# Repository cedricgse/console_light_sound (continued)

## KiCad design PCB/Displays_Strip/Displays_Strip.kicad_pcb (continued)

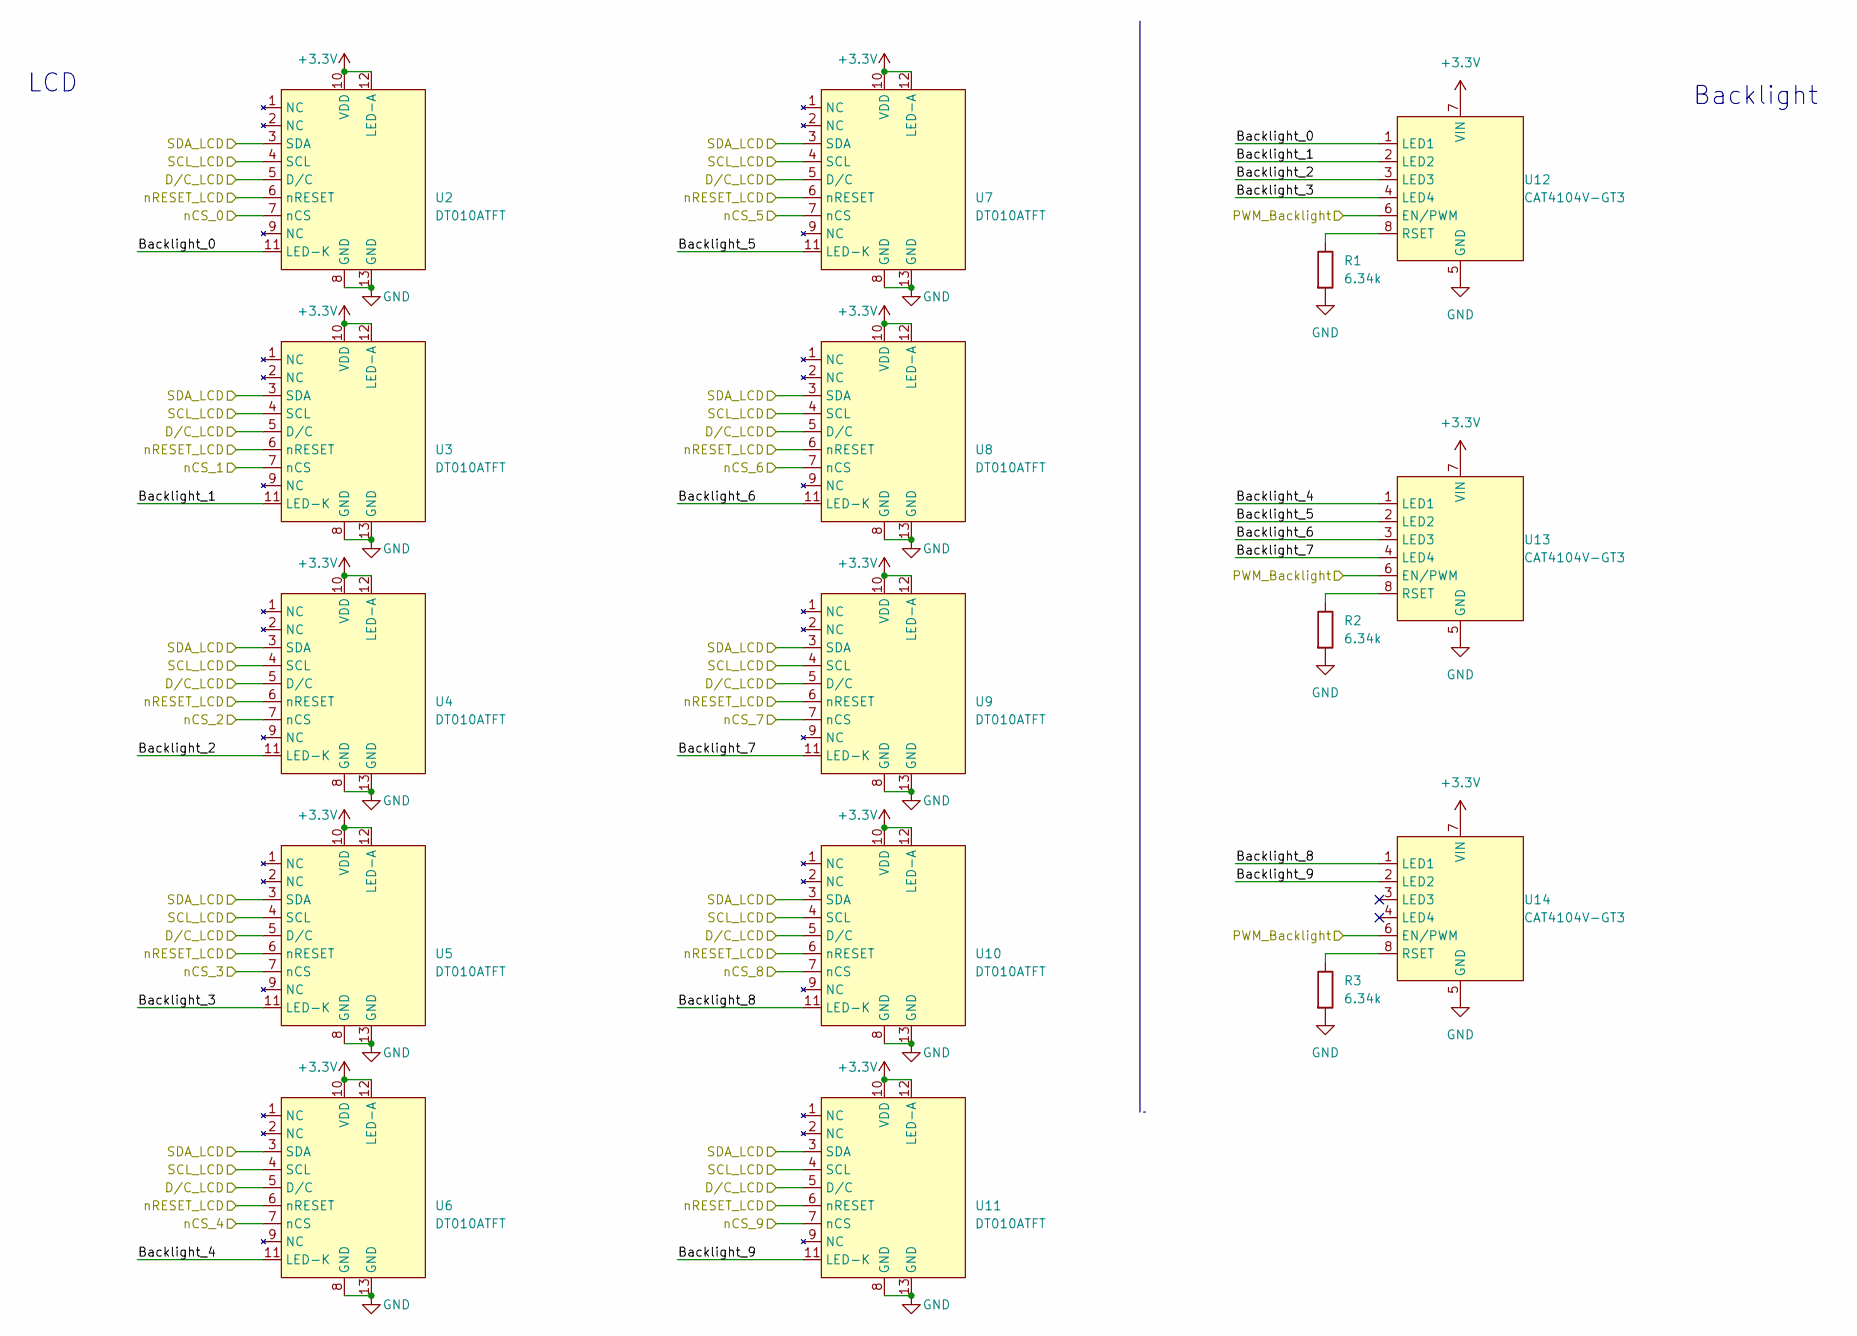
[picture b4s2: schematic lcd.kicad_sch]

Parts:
R1, R2, R3: 6.34k; R_0805_2012Metric
U2, U3, U4, U5, U6, U7, U8, U9, U10, U11: DT010ATFT; Hirose FFC FPC 13 Pin Inverted
U12, U13, U14: CAT4104V-GT3; SOIC-8_3.9x4.9mm_P1.27mm

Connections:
+3.3V: U2.10 (VDD), U2.12 (LED-A), U3.10 (VDD), U3.12 (LED-A), U4.10 (VDD), U4.12 (LED-A), U5.10 (VDD), U5.12 (LED-A), U6.10 (VDD), U6.12 (LED-A), U7.10 (VDD), U7.12 (LED-A), U8.10 (VDD), U8.12 (LED-A), U9.10 (VDD), U9.12 (LED-A), U10.10 (VDD), U10.12 (LED-A), U11.10 (VDD), U11.12 (LED-A), U12.7 (VIN), U13.7 (VIN), U14.7 (VIN); also elsewhere on the board
/D/C_LCD: U2.5 (D/C), U3.5 (D/C), U4.5 (D/C), U5.5 (D/C), U6.5 (D/C), U7.5 (D/C), U8.5 (D/C), U9.5 (D/C), U10.5 (D/C), U11.5 (D/C); also elsewhere on the board
/LCDs/Backlight_0: U2.11 (LED-K), U12.1 (LED1)
/LCDs/Backlight_1: U3.11 (LED-K), U12.2 (LED2)
/LCDs/Backlight_2: U4.11 (LED-K), U12.3 (LED3)
/LCDs/Backlight_3: U5.11 (LED-K), U12.4 (LED4)
/LCDs/Backlight_4: U6.11 (LED-K), U13.1 (LED1)
/LCDs/Backlight_5: U7.11 (LED-K), U13.2 (LED2)
/LCDs/Backlight_6: U8.11 (LED-K), U13.3 (LED3)
/LCDs/Backlight_7: U9.11 (LED-K), U13.4 (LED4)
/LCDs/Backlight_8: U10.11 (LED-K), U14.1 (LED1)
/LCDs/Backlight_9: U11.11 (LED-K), U14.2 (LED2)
/PWM_LCD: U12.6 (EN/PWM), U13.6 (EN/PWM), U14.6 (EN/PWM); also elsewhere on the board
/SCK_LCD: U2.4 (SCL), U3.4 (SCL), U4.4 (SCL), U5.4 (SCL), U6.4 (SCL), U7.4 (SCL), U8.4 (SCL), U9.4 (SCL), U10.4 (SCL), U11.4 (SCL); also elsewhere on the board
/SDA_LCD: U2.3 (SDA), U3.3 (SDA), U4.3 (SDA), U5.3 (SDA), U6.3 (SDA), U7.3 (SDA), U8.3 (SDA), U9.3 (SDA), U10.3 (SDA), U11.3 (SDA); also elsewhere on the board
/nCS_0: U2.7 (nCS); also elsewhere on the board
/nCS_1: U3.7 (nCS); also elsewhere on the board
/nCS_2: U4.7 (nCS); also elsewhere on the board
/nCS_3: U5.7 (nCS); also elsewhere on the board
/nCS_4: U6.7 (nCS); also elsewhere on the board
/nCS_5: U7.7 (nCS); also elsewhere on the board
/nCS_6: U8.7 (nCS); also elsewhere on the board
/nCS_7: U9.7 (nCS); also elsewhere on the board
/nCS_8: U10.7 (nCS); also elsewhere on the board
/nCS_9: U11.7 (nCS); also elsewhere on the board
/nRESET_LCD: U2.6 (nRESET), U3.6 (nRESET), U4.6 (nRESET), U5.6 (nRESET), U6.6 (nRESET), U7.6 (nRESET), U8.6 (nRESET), U9.6 (nRESET), U10.6 (nRESET), U11.6 (nRESET); also elsewhere on the board
GND: R1.2, R2.2, R3.2, U2.8 (GND), U2.13 (GND), U3.8 (GND), U3.13 (GND), U4.8 (GND), U4.13 (GND), U5.8 (GND), U5.13 (GND), U6.8 (GND), U6.13 (GND), U7.8 (GND), U7.13 (GND), U8.8 (GND), U8.13 (GND), U9.8 (GND), U9.13 (GND), U10.8 (GND), U10.13 (GND), U11.8 (GND), U11.13 (GND), U12.5 (GND), U13.5 (GND), U14.5 (GND); also elsewhere on the board
unnamed: R1.1, U12.8 (RSET)
unnamed: R2.1, U13.8 (RSET)
unnamed: R3.1, U14.8 (RSET)

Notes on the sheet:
LCD
Backlight

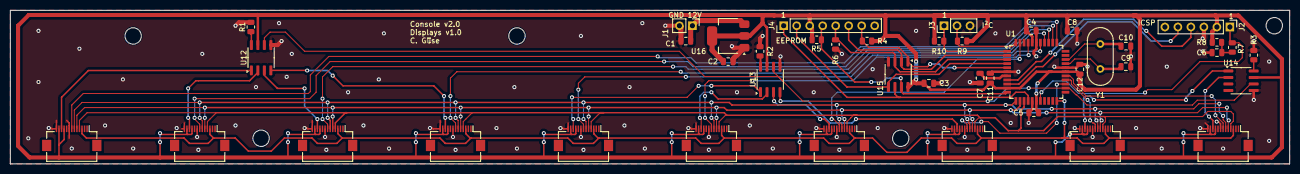
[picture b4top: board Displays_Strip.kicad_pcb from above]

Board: 2 copper layers, 250.0 x 30.0 mm, 48 parts (0 on the bottom side), 46 nets.

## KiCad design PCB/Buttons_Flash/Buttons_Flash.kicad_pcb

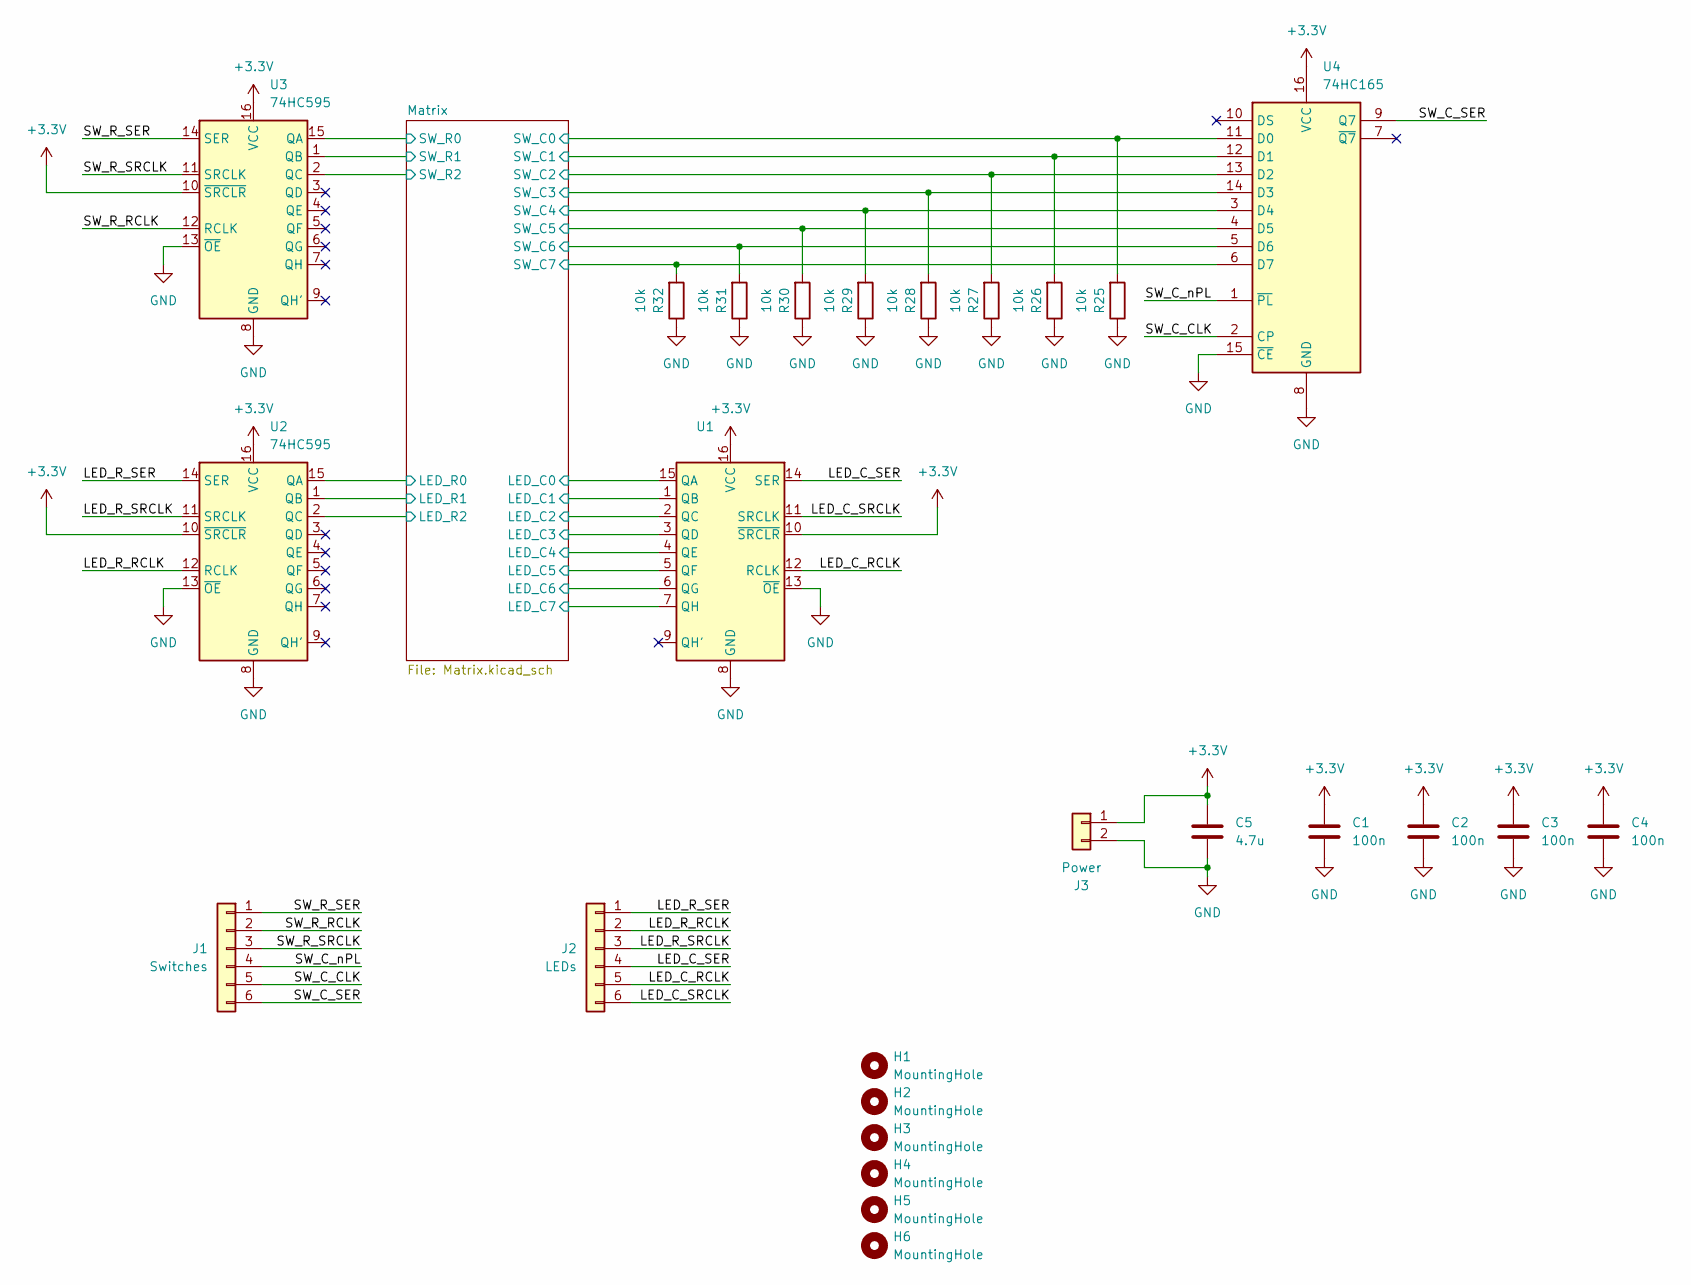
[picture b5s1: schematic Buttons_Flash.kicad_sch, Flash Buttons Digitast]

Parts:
C1, C2, C3, C4: 100n; C_0805_2012Metric
C5: 4.7u; C_0805_2012Metric
H1, H2, H3, H4, H5, H6: MountingHole; MountingHole_3.2mm_M3
J1: Switches; PinHeader_1x06_P2.54mm_Vertical
J2: LEDs; PinHeader_1x06_P2.54mm_Vertical
J3: Power; PinHeader_1x02_P2.54mm_Vertical
R25, R26, R27, R28, R29, R30, R31, R32: 10k; R_0805_2012Metric
U1, U2, U3: 74HC595; SO-16_3.9x9.9mm_P1.27mm
U4: 74HC165; SO-16_3.9x9.9mm_P1.27mm

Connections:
+3.3V: C1.1, C2.1, C3.1, C4.1, C5.1, J3.1, U1.10 (~SRCLR), U1.16 (VCC), U2.10 (~SRCLR), U2.16 (VCC), U3.10 (~SRCLR), U3.16 (VCC), U4.16 (VCC)
/LED_C_RCLK: J2.5, U1.12 (RCLK)
/LED_C_SER: J2.4, U1.14 (SER)
/LED_C_SRCLK: J2.6, U1.11 (SRCLK)
/LED_R_RCLK: J2.2, U2.12 (RCLK)
/LED_R_SER: J2.1, U2.14 (SER)
/LED_R_SRCLK: J2.3, U2.11 (SRCLK)
/Matrix/LED_C0: U1.15 (QA); also elsewhere on the board
/Matrix/LED_C1: U1.1 (QB); also elsewhere on the board
/Matrix/LED_C2: U1.2 (QC); also elsewhere on the board
/Matrix/LED_C3: U1.3 (QD); also elsewhere on the board
/Matrix/LED_C4: U1.4 (QE); also elsewhere on the board
/Matrix/LED_C5: U1.5 (QF); also elsewhere on the board
/Matrix/LED_C6: U1.6 (QG); also elsewhere on the board
/Matrix/LED_C7: U1.7 (QH); also elsewhere on the board
/Matrix/LED_R0: U2.15 (QA); also elsewhere on the board
/Matrix/LED_R1: U2.1 (QB); also elsewhere on the board
/Matrix/LED_R2: U2.2 (QC); also elsewhere on the board
/Matrix/SW_C0: R25.2, U4.11 (D0); also elsewhere on the board
/Matrix/SW_C1: R26.2, U4.12 (D1); also elsewhere on the board
/Matrix/SW_C2: R27.2, U4.13 (D2); also elsewhere on the board
/Matrix/SW_C3: R28.2, U4.14 (D3); also elsewhere on the board
/Matrix/SW_C4: R29.2, U4.3 (D4); also elsewhere on the board
/Matrix/SW_C5: R30.2, U4.4 (D5); also elsewhere on the board
/Matrix/SW_C6: R31.2, U4.5 (D6); also elsewhere on the board
/Matrix/SW_C7: R32.2, U4.6 (D7); also elsewhere on the board
/Matrix/SW_R0: U3.15 (QA); also elsewhere on the board
/Matrix/SW_R1: U3.1 (QB); also elsewhere on the board
/Matrix/SW_R2: U3.2 (QC); also elsewhere on the board
/SW_C_CLK: J1.5, U4.2 (CP)
/SW_C_SER: J1.6, U4.9 (Q7)
/SW_C_nPL: J1.4, U4.1 (~PL)
/SW_R_RCLK: J1.2, U3.12 (RCLK)
/SW_R_SER: J1.1, U3.14 (SER)
/SW_R_SRCLK: J1.3, U3.11 (SRCLK)
GND: C1.2, C2.2, C3.2, C4.2, C5.2, J3.2, R25.1, R26.1, R27.1, R28.1, R29.1, R30.1, R31.1, R32.1, U1.8 (GND), U1.13 (~OE), U2.8 (GND), U2.13 (~OE), U3.8 (GND), U3.13 (~OE), U4.8 (GND), U4.15 (~CE)

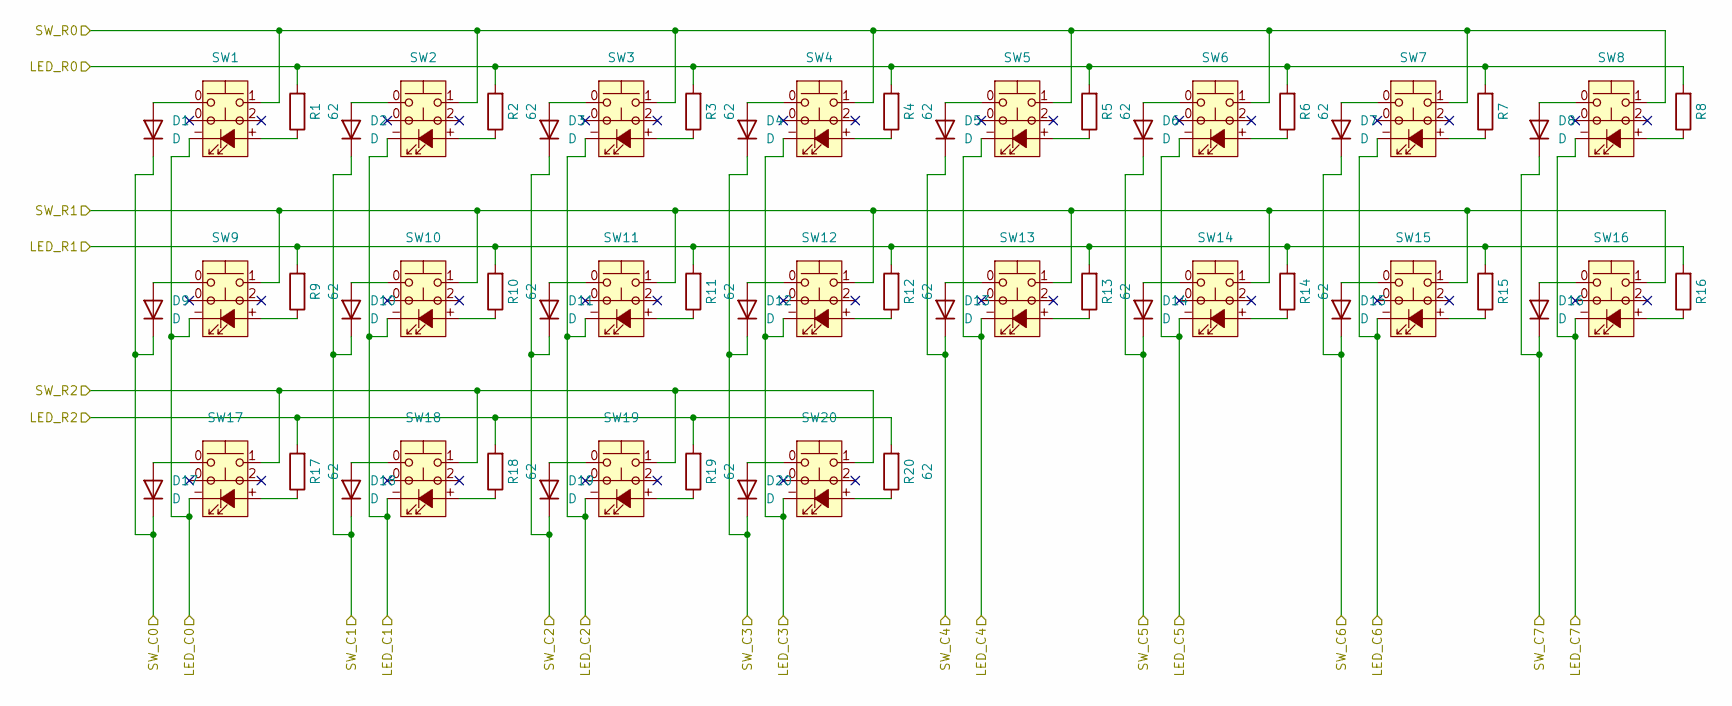
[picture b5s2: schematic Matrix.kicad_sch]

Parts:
D1, D2, D3, D4, D5, D6, D7, D8, D9, D10, D11, D12, D13, D14, D15, D16, D17, D18, D19, D20: D; D_0805_2012Metric
R1, R2, R3, R4, R5, R6, R7, R8, R9, R10, R11, R12, R13, R14, R15, R16, R17, R18, R19, R20: 62; R_0805_2012Metric
SW1, SW2, SW3, SW4, SW5, SW6, SW7, SW8, SW9, SW10, SW11, SW12, SW13, SW14, SW15, SW16, SW17, SW18, SW19, SW20: Digitast

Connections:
/Matrix/LED_C0: SW1.-, SW9.-, SW17.-; also elsewhere on the board
/Matrix/LED_C1: SW2.-, SW10.-, SW18.-; also elsewhere on the board
/Matrix/LED_C2: SW3.-, SW11.-, SW19.-; also elsewhere on the board
/Matrix/LED_C3: SW4.-, SW12.-, SW20.-; also elsewhere on the board
/Matrix/LED_C4: SW5.-, SW13.-; also elsewhere on the board
/Matrix/LED_C5: SW6.-, SW14.-; also elsewhere on the board
/Matrix/LED_C6: SW7.-, SW15.-; also elsewhere on the board
/Matrix/LED_C7: SW8.-, SW16.-; also elsewhere on the board
/Matrix/LED_R0: R1.2, R2.2, R3.2, R4.2, R5.2, R6.2, R7.2, R8.2; also elsewhere on the board
/Matrix/LED_R1: R9.2, R10.2, R11.2, R12.2, R13.2, R14.2, R15.2, R16.2; also elsewhere on the board
/Matrix/LED_R2: R17.2, R18.2, R19.2, R20.2; also elsewhere on the board
/Matrix/SW_C0: D1.1 (K), D9.1 (K), D17.1 (K); also elsewhere on the board
/Matrix/SW_C1: D2.1 (K), D10.1 (K), D18.1 (K); also elsewhere on the board
/Matrix/SW_C2: D3.1 (K), D11.1 (K), D19.1 (K); also elsewhere on the board
/Matrix/SW_C3: D4.1 (K), D12.1 (K), D20.1 (K); also elsewhere on the board
/Matrix/SW_C4: D5.1 (K), D13.1 (K); also elsewhere on the board
/Matrix/SW_C5: D6.1 (K), D14.1 (K); also elsewhere on the board
/Matrix/SW_C6: D7.1 (K), D15.1 (K); also elsewhere on the board
/Matrix/SW_C7: D8.1 (K), D16.1 (K); also elsewhere on the board
/Matrix/SW_R0: SW1.1, SW2.1, SW3.1, SW4.1, SW5.1, SW6.1, SW7.1, SW8.1; also elsewhere on the board
/Matrix/SW_R1: SW9.1, SW10.1, SW11.1, SW12.1, SW13.1, SW14.1, SW15.1, SW16.1; also elsewhere on the board
/Matrix/SW_R2: SW17.1, SW18.1, SW19.1, SW20.1; also elsewhere on the board
unnamed: D1.2 (A), SW1.0
unnamed: D2.2 (A), SW2.0
unnamed: D3.2 (A), SW3.0
unnamed: D4.2 (A), SW4.0
unnamed: D5.2 (A), SW5.0
unnamed: D6.2 (A), SW6.0
unnamed: D7.2 (A), SW7.0
unnamed: D8.2 (A), SW8.0
unnamed: D9.2 (A), SW9.0
unnamed: D10.2 (A), SW10.0
unnamed: D11.2 (A), SW11.0
unnamed: D12.2 (A), SW12.0
unnamed: D13.2 (A), SW13.0
unnamed: D14.2 (A), SW14.0
unnamed: D15.2 (A), SW15.0
unnamed: D16.2 (A), SW16.0
unnamed: D17.2 (A), SW17.0
unnamed: D18.2 (A), SW18.0
unnamed: D19.2 (A), SW19.0
unnamed: D20.2 (A), SW20.0
unnamed: R1.1, SW1.+
unnamed: R2.1, SW2.+
unnamed: R3.1, SW3.+
unnamed: R4.1, SW4.+
unnamed: R5.1, SW5.+
unnamed: R6.1, SW6.+
unnamed: R7.1, SW7.+
unnamed: R8.1, SW8.+
unnamed: R9.1, SW9.+
unnamed: R10.1, SW10.+
unnamed: R11.1, SW11.+
unnamed: R12.1, SW12.+
unnamed: R13.1, SW13.+
unnamed: R14.1, SW14.+
unnamed: R15.1, SW15.+
unnamed: R16.1, SW16.+
unnamed: R17.1, SW17.+
unnamed: R18.1, SW18.+
unnamed: R19.1, SW19.+
unnamed: R20.1, SW20.+

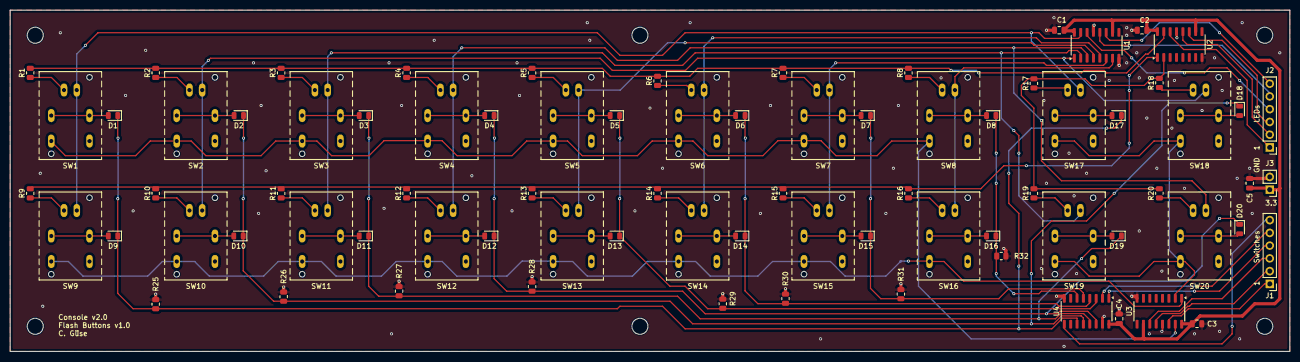
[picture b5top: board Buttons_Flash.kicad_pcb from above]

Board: 2 copper layers, 255.0 x 68.0 mm, 86 parts (0 on the bottom side), 76 nets.

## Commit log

2024-09-14 Schematic Displays
2024-09-16 Schematic Flash
2024-09-17 PCB Buttons Flash
2024-09-18 PCB Displays
2024-09-19 Fader Breakout Board
2024-09-20 Keys Flash
2024-09-21 Keyboard
2024-09-22 Motorfader
